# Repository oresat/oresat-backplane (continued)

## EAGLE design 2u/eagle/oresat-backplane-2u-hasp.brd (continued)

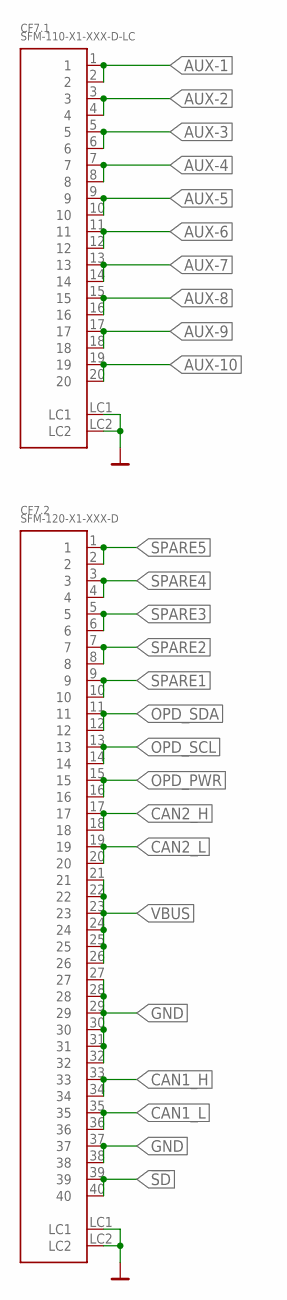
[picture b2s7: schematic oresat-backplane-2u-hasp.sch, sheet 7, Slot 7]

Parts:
CF7.1: SFM-110-X1-XXX-D-LC
CF7.2: SFM-120-X1-XXX-D

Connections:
!SD: CF7.2.39, CF7.2.40; also elsewhere on the board
AUX-1: CF7.1.1, CF7.1.2; also elsewhere on the board
AUX-2: CF7.1.3, CF7.1.4; also elsewhere on the board
AUX-3: CF7.1.5, CF7.1.6; also elsewhere on the board
AUX-4: CF7.1.7, CF7.1.8; also elsewhere on the board
AUX-5: CF7.1.9, CF7.1.10; also elsewhere on the board
AUX-6: CF7.1.11, CF7.1.12; also elsewhere on the board
AUX-7: CF7.1.13, CF7.1.14; also elsewhere on the board
AUX-8: CF7.1.15, CF7.1.16; also elsewhere on the board
AUX-9: CF7.1.17, CF7.1.18; also elsewhere on the board
AUX-10: CF7.1.19, CF7.1.20; also elsewhere on the board
CAN1_H: CF7.2.33, CF7.2.34; also elsewhere on the board
CAN1_L: CF7.2.35, CF7.2.36; also elsewhere on the board
CAN2_H: CF7.2.17, CF7.2.18; also elsewhere on the board
CAN2_L: CF7.2.19, CF7.2.20; also elsewhere on the board
GND: CF7.1.LC1, CF7.1.LC2, CF7.2.27, CF7.2.28, CF7.2.29, CF7.2.30, CF7.2.31, CF7.2.32, CF7.2.37, CF7.2.38, CF7.2.LC1, CF7.2.LC2; also elsewhere on the board
OPD_PWR: CF7.2.15, CF7.2.16; also elsewhere on the board
OPD_SCL: CF7.2.13, CF7.2.14; also elsewhere on the board
OPD_SDA: CF7.2.11, CF7.2.12; also elsewhere on the board
SPARE1: CF7.2.9, CF7.2.10; also elsewhere on the board
SPARE2: CF7.2.7, CF7.2.8; also elsewhere on the board
SPARE3: CF7.2.5, CF7.2.6; also elsewhere on the board
SPARE4: CF7.2.3, CF7.2.4; also elsewhere on the board
SPARE5: CF7.2.1, CF7.2.2; also elsewhere on the board
VBUS: CF7.2.21, CF7.2.22, CF7.2.23, CF7.2.24, CF7.2.25, CF7.2.26; also elsewhere on the board

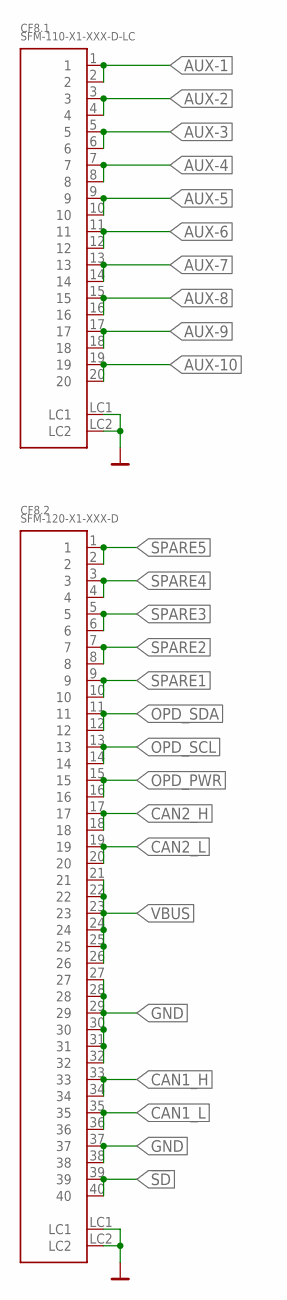
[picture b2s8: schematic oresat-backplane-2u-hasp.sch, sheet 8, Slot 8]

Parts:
CF8.1: SFM-110-X1-XXX-D-LC
CF8.2: SFM-120-X1-XXX-D

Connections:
!SD: CF8.2.39, CF8.2.40; also elsewhere on the board
AUX-1: CF8.1.1, CF8.1.2; also elsewhere on the board
AUX-2: CF8.1.3, CF8.1.4; also elsewhere on the board
AUX-3: CF8.1.5, CF8.1.6; also elsewhere on the board
AUX-4: CF8.1.7, CF8.1.8; also elsewhere on the board
AUX-5: CF8.1.9, CF8.1.10; also elsewhere on the board
AUX-6: CF8.1.11, CF8.1.12; also elsewhere on the board
AUX-7: CF8.1.13, CF8.1.14; also elsewhere on the board
AUX-8: CF8.1.15, CF8.1.16; also elsewhere on the board
AUX-9: CF8.1.17, CF8.1.18; also elsewhere on the board
AUX-10: CF8.1.19, CF8.1.20; also elsewhere on the board
CAN1_H: CF8.2.33, CF8.2.34; also elsewhere on the board
CAN1_L: CF8.2.35, CF8.2.36; also elsewhere on the board
CAN2_H: CF8.2.17, CF8.2.18; also elsewhere on the board
CAN2_L: CF8.2.19, CF8.2.20; also elsewhere on the board
GND: CF8.1.LC1, CF8.1.LC2, CF8.2.27, CF8.2.28, CF8.2.29, CF8.2.30, CF8.2.31, CF8.2.32, CF8.2.37, CF8.2.38, CF8.2.LC1, CF8.2.LC2; also elsewhere on the board
OPD_PWR: CF8.2.15, CF8.2.16; also elsewhere on the board
OPD_SCL: CF8.2.13, CF8.2.14; also elsewhere on the board
OPD_SDA: CF8.2.11, CF8.2.12; also elsewhere on the board
SPARE1: CF8.2.9, CF8.2.10; also elsewhere on the board
SPARE2: CF8.2.7, CF8.2.8; also elsewhere on the board
SPARE3: CF8.2.5, CF8.2.6; also elsewhere on the board
SPARE4: CF8.2.3, CF8.2.4; also elsewhere on the board
SPARE5: CF8.2.1, CF8.2.2; also elsewhere on the board
VBUS: CF8.2.21, CF8.2.22, CF8.2.23, CF8.2.24, CF8.2.25, CF8.2.26; also elsewhere on the board

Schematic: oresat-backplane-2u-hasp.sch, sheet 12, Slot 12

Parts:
CF12.1: SFM-110-X1-XXX-D-LC
CF12.2: SFM-120-X1-XXX-D

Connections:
!SD: CF12.2.39, CF12.2.40; also elsewhere on the board
AUX-1: CF12.1.1, CF12.1.2; also elsewhere on the board
AUX-2: CF12.1.3, CF12.1.4; also elsewhere on the board
AUX-3: CF12.1.5, CF12.1.6; also elsewhere on the board
AUX-4: CF12.1.7, CF12.1.8; also elsewhere on the board
AUX-5: CF12.1.9, CF12.1.10; also elsewhere on the board
AUX-6: CF12.1.11, CF12.1.12; also elsewhere on the board
AUX-7: CF12.1.13, CF12.1.14; also elsewhere on the board
AUX-8: CF12.1.15, CF12.1.16; also elsewhere on the board
AUX-9: CF12.1.17, CF12.1.18; also elsewhere on the board
AUX-10: CF12.1.19, CF12.1.20; also elsewhere on the board
CAN1_H: CF12.2.33, CF12.2.34; also elsewhere on the board
CAN1_L: CF12.2.35, CF12.2.36; also elsewhere on the board
CAN2_H: CF12.2.17, CF12.2.18; also elsewhere on the board
CAN2_L: CF12.2.19, CF12.2.20; also elsewhere on the board
GND: CF12.1.LC1, CF12.1.LC2, CF12.2.27, CF12.2.28, CF12.2.29, CF12.2.30, CF12.2.31, CF12.2.32, CF12.2.37, CF12.2.38, CF12.2.LC1, CF12.2.LC2; also elsewhere on the board
OPD_PWR: CF12.2.15, CF12.2.16; also elsewhere on the board
OPD_SCL: CF12.2.13, CF12.2.14; also elsewhere on the board
OPD_SDA: CF12.2.11, CF12.2.12; also elsewhere on the board
SPARE1: CF12.2.9, CF12.2.10; also elsewhere on the board
SPARE2: CF12.2.7, CF12.2.8; also elsewhere on the board
SPARE3: CF12.2.5, CF12.2.6; also elsewhere on the board
SPARE4: CF12.2.3, CF12.2.4; also elsewhere on the board
SPARE5: CF12.2.1, CF12.2.2; also elsewhere on the board
VBUS: CF12.2.21, CF12.2.22, CF12.2.23, CF12.2.24, CF12.2.25, CF12.2.26; also elsewhere on the board

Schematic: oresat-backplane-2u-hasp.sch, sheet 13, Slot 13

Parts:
CF13.1: SFM-110-X1-XXX-D-LC
CF13.2: SFM-120-X1-XXX-D

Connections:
!SD: CF13.2.39, CF13.2.40; also elsewhere on the board
AUX-1: CF13.1.1, CF13.1.2; also elsewhere on the board
AUX-2: CF13.1.3, CF13.1.4; also elsewhere on the board
AUX-3: CF13.1.5, CF13.1.6; also elsewhere on the board
AUX-4: CF13.1.7, CF13.1.8; also elsewhere on the board
AUX-5: CF13.1.9, CF13.1.10; also elsewhere on the board
AUX-6: CF13.1.11, CF13.1.12; also elsewhere on the board
AUX-7: CF13.1.13, CF13.1.14; also elsewhere on the board
AUX-8: CF13.1.15, CF13.1.16; also elsewhere on the board
AUX-9: CF13.1.17, CF13.1.18; also elsewhere on the board
AUX-10: CF13.1.19, CF13.1.20; also elsewhere on the board
CAN1_H: CF13.2.33, CF13.2.34; also elsewhere on the board
CAN1_L: CF13.2.35, CF13.2.36; also elsewhere on the board
CAN2_H: CF13.2.17, CF13.2.18; also elsewhere on the board
CAN2_L: CF13.2.19, CF13.2.20; also elsewhere on the board
GND: CF13.1.LC1, CF13.1.LC2, CF13.2.27, CF13.2.28, CF13.2.29, CF13.2.30, CF13.2.31, CF13.2.32, CF13.2.37, CF13.2.38, CF13.2.LC1, CF13.2.LC2; also elsewhere on the board
OPD_PWR: CF13.2.15, CF13.2.16; also elsewhere on the board
OPD_SCL: CF13.2.13, CF13.2.14; also elsewhere on the board
OPD_SDA: CF13.2.11, CF13.2.12; also elsewhere on the board
SPARE1: CF13.2.9, CF13.2.10; also elsewhere on the board
SPARE2: CF13.2.7, CF13.2.8; also elsewhere on the board
SPARE3: CF13.2.5, CF13.2.6; also elsewhere on the board
SPARE4: CF13.2.3, CF13.2.4; also elsewhere on the board
SPARE5: CF13.2.1, CF13.2.2; also elsewhere on the board
VBUS: CF13.2.21, CF13.2.22, CF13.2.23, CF13.2.24, CF13.2.25, CF13.2.26; also elsewhere on the board

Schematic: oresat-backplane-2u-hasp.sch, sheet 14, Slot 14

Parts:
CF14.1: SFM-110-X1-XXX-D-LC
CF14.2: SFM-120-X1-XXX-D

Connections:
!SD: CF14.2.39, CF14.2.40; also elsewhere on the board
AUX-1: CF14.1.1, CF14.1.2; also elsewhere on the board
AUX-2: CF14.1.3, CF14.1.4; also elsewhere on the board
AUX-3: CF14.1.5, CF14.1.6; also elsewhere on the board
AUX-4: CF14.1.7, CF14.1.8; also elsewhere on the board
AUX-5: CF14.1.9, CF14.1.10; also elsewhere on the board
AUX-6: CF14.1.11, CF14.1.12; also elsewhere on the board
AUX-7: CF14.1.13, CF14.1.14; also elsewhere on the board
AUX-8: CF14.1.15, CF14.1.16; also elsewhere on the board
AUX-9: CF14.1.17, CF14.1.18; also elsewhere on the board
AUX-10: CF14.1.19, CF14.1.20; also elsewhere on the board
CAN1_H: CF14.2.33, CF14.2.34; also elsewhere on the board
CAN1_L: CF14.2.35, CF14.2.36; also elsewhere on the board
CAN2_H: CF14.2.17, CF14.2.18; also elsewhere on the board
CAN2_L: CF14.2.19, CF14.2.20; also elsewhere on the board
GND: CF14.1.LC1, CF14.1.LC2, CF14.2.27, CF14.2.28, CF14.2.29, CF14.2.30, CF14.2.31, CF14.2.32, CF14.2.37, CF14.2.38, CF14.2.LC1, CF14.2.LC2; also elsewhere on the board
OPD_PWR: CF14.2.15, CF14.2.16; also elsewhere on the board
OPD_SCL: CF14.2.13, CF14.2.14; also elsewhere on the board
OPD_SDA: CF14.2.11, CF14.2.12; also elsewhere on the board
SPARE1: CF14.2.9, CF14.2.10; also elsewhere on the board
SPARE2: CF14.2.7, CF14.2.8; also elsewhere on the board
SPARE3: CF14.2.5, CF14.2.6; also elsewhere on the board
SPARE4: CF14.2.3, CF14.2.4; also elsewhere on the board
SPARE5: CF14.2.1, CF14.2.2; also elsewhere on the board
VBUS: CF14.2.21, CF14.2.22, CF14.2.23, CF14.2.24, CF14.2.25, CF14.2.26; also elsewhere on the board

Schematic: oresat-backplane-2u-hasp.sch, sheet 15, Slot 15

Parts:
CF15.1: SFM-110-X1-XXX-D-LC
CF15.2: SFM-120-X1-XXX-D

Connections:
!SD: CF15.2.39, CF15.2.40; also elsewhere on the board
AUX-1: CF15.1.1, CF15.1.2; also elsewhere on the board
AUX-2: CF15.1.3, CF15.1.4; also elsewhere on the board
AUX-3: CF15.1.5, CF15.1.6; also elsewhere on the board
AUX-4: CF15.1.7, CF15.1.8; also elsewhere on the board
AUX-5: CF15.1.9, CF15.1.10; also elsewhere on the board
AUX-6: CF15.1.11, CF15.1.12; also elsewhere on the board
AUX-7: CF15.1.13, CF15.1.14; also elsewhere on the board
AUX-8: CF15.1.15, CF15.1.16; also elsewhere on the board
AUX-9: CF15.1.17, CF15.1.18; also elsewhere on the board
AUX-10: CF15.1.19, CF15.1.20; also elsewhere on the board
CAN1_H: CF15.2.33, CF15.2.34; also elsewhere on the board
CAN1_L: CF15.2.35, CF15.2.36; also elsewhere on the board
CAN2_H: CF15.2.17, CF15.2.18; also elsewhere on the board
CAN2_L: CF15.2.19, CF15.2.20; also elsewhere on the board
GND: CF15.1.LC1, CF15.1.LC2, CF15.2.27, CF15.2.28, CF15.2.29, CF15.2.30, CF15.2.31, CF15.2.32, CF15.2.37, CF15.2.38, CF15.2.LC1, CF15.2.LC2; also elsewhere on the board
OPD_PWR: CF15.2.15, CF15.2.16; also elsewhere on the board
OPD_SCL: CF15.2.13, CF15.2.14; also elsewhere on the board
OPD_SDA: CF15.2.11, CF15.2.12; also elsewhere on the board
SPARE1: CF15.2.9, CF15.2.10; also elsewhere on the board
SPARE2: CF15.2.7, CF15.2.8; also elsewhere on the board
SPARE3: CF15.2.5, CF15.2.6; also elsewhere on the board
SPARE4: CF15.2.3, CF15.2.4; also elsewhere on the board
SPARE5: CF15.2.1, CF15.2.2; also elsewhere on the board
VBUS: CF15.2.21, CF15.2.22, CF15.2.23, CF15.2.24, CF15.2.25, CF15.2.26; also elsewhere on the board

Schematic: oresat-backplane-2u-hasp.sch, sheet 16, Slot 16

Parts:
CF16.1: SFM-110-X1-XXX-D-LC
CF16.2: SFM-120-X1-XXX-D

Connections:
!SD: CF16.2.39, CF16.2.40; also elsewhere on the board
AUX-1: CF16.1.1, CF16.1.2; also elsewhere on the board
AUX-2: CF16.1.3, CF16.1.4; also elsewhere on the board
AUX-3: CF16.1.5, CF16.1.6; also elsewhere on the board
AUX-4: CF16.1.7, CF16.1.8; also elsewhere on the board
AUX-5: CF16.1.9, CF16.1.10; also elsewhere on the board
AUX-6: CF16.1.11, CF16.1.12; also elsewhere on the board
AUX-7: CF16.1.13, CF16.1.14; also elsewhere on the board
AUX-8: CF16.1.15, CF16.1.16; also elsewhere on the board
AUX-9: CF16.1.17, CF16.1.18; also elsewhere on the board
AUX-10: CF16.1.19, CF16.1.20; also elsewhere on the board
CAN1_H: CF16.2.33, CF16.2.34; also elsewhere on the board
CAN1_L: CF16.2.35, CF16.2.36; also elsewhere on the board
CAN2_H: CF16.2.17, CF16.2.18; also elsewhere on the board
CAN2_L: CF16.2.19, CF16.2.20; also elsewhere on the board
GND: CF16.1.LC1, CF16.1.LC2, CF16.2.27, CF16.2.28, CF16.2.29, CF16.2.30, CF16.2.31, CF16.2.32, CF16.2.37, CF16.2.38, CF16.2.LC1, CF16.2.LC2; also elsewhere on the board
OPD_PWR: CF16.2.15, CF16.2.16; also elsewhere on the board
OPD_SCL: CF16.2.13, CF16.2.14; also elsewhere on the board
OPD_SDA: CF16.2.11, CF16.2.12; also elsewhere on the board
SPARE1: CF16.2.9, CF16.2.10; also elsewhere on the board
SPARE2: CF16.2.7, CF16.2.8; also elsewhere on the board
SPARE3: CF16.2.5, CF16.2.6; also elsewhere on the board
SPARE4: CF16.2.3, CF16.2.4; also elsewhere on the board
SPARE5: CF16.2.1, CF16.2.2; also elsewhere on the board
VBUS: CF16.2.21, CF16.2.22, CF16.2.23, CF16.2.24, CF16.2.25, CF16.2.26; also elsewhere on the board

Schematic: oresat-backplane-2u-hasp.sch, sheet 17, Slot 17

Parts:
CF17.1: SFM-110-X1-XXX-D-LC
CF17.2: SFM-120-X1-XXX-D

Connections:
!SD: CF17.2.39, CF17.2.40; also elsewhere on the board
AUX-1: CF17.1.1, CF17.1.2; also elsewhere on the board
AUX-2: CF17.1.3, CF17.1.4; also elsewhere on the board
AUX-3: CF17.1.5, CF17.1.6; also elsewhere on the board
AUX-4: CF17.1.7, CF17.1.8; also elsewhere on the board
AUX-5: CF17.1.9, CF17.1.10; also elsewhere on the board
AUX-6: CF17.1.11, CF17.1.12; also elsewhere on the board
AUX-7: CF17.1.13, CF17.1.14; also elsewhere on the board
AUX-8: CF17.1.15, CF17.1.16; also elsewhere on the board
AUX-9: CF17.1.17, CF17.1.18; also elsewhere on the board
AUX-10: CF17.1.19, CF17.1.20; also elsewhere on the board
CAN1_H: CF17.2.33, CF17.2.34; also elsewhere on the board
CAN1_L: CF17.2.35, CF17.2.36; also elsewhere on the board
CAN2_H: CF17.2.17, CF17.2.18; also elsewhere on the board
CAN2_L: CF17.2.19, CF17.2.20; also elsewhere on the board
GND: CF17.1.LC1, CF17.1.LC2, CF17.2.27, CF17.2.28, CF17.2.29, CF17.2.30, CF17.2.31, CF17.2.32, CF17.2.37, CF17.2.38, CF17.2.LC1, CF17.2.LC2; also elsewhere on the board
OPD_PWR: CF17.2.15, CF17.2.16; also elsewhere on the board
OPD_SCL: CF17.2.13, CF17.2.14; also elsewhere on the board
OPD_SDA: CF17.2.11, CF17.2.12; also elsewhere on the board
SPARE1: CF17.2.9, CF17.2.10; also elsewhere on the board
SPARE2: CF17.2.7, CF17.2.8; also elsewhere on the board
SPARE3: CF17.2.5, CF17.2.6; also elsewhere on the board
SPARE4: CF17.2.3, CF17.2.4; also elsewhere on the board
SPARE5: CF17.2.1, CF17.2.2; also elsewhere on the board
VBUS: CF17.2.21, CF17.2.22, CF17.2.23, CF17.2.24, CF17.2.25, CF17.2.26; also elsewhere on the board

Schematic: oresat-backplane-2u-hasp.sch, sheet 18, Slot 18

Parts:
CF18.1: SFM-110-X1-XXX-D-LC
CF18.2: SFM-120-X1-XXX-D

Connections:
!SD: CF18.2.39, CF18.2.40; also elsewhere on the board
AUX-1: CF18.1.1, CF18.1.2; also elsewhere on the board
AUX-2: CF18.1.3, CF18.1.4; also elsewhere on the board
AUX-3: CF18.1.5, CF18.1.6; also elsewhere on the board
AUX-4: CF18.1.7, CF18.1.8; also elsewhere on the board
AUX-5: CF18.1.9, CF18.1.10; also elsewhere on the board
AUX-6: CF18.1.11, CF18.1.12; also elsewhere on the board
AUX-7: CF18.1.13, CF18.1.14; also elsewhere on the board
AUX-8: CF18.1.15, CF18.1.16; also elsewhere on the board
AUX-9: CF18.1.17, CF18.1.18; also elsewhere on the board
AUX-10: CF18.1.19, CF18.1.20; also elsewhere on the board
CAN1_H: CF18.2.33, CF18.2.34; also elsewhere on the board
CAN1_L: CF18.2.35, CF18.2.36; also elsewhere on the board
CAN2_H: CF18.2.17, CF18.2.18; also elsewhere on the board
CAN2_L: CF18.2.19, CF18.2.20; also elsewhere on the board
GND: CF18.1.LC1, CF18.1.LC2, CF18.2.27, CF18.2.28, CF18.2.29, CF18.2.30, CF18.2.31, CF18.2.32, CF18.2.37, CF18.2.38, CF18.2.LC1, CF18.2.LC2; also elsewhere on the board
OPD_PWR: CF18.2.15, CF18.2.16; also elsewhere on the board
OPD_SCL: CF18.2.13, CF18.2.14; also elsewhere on the board
OPD_SDA: CF18.2.11, CF18.2.12; also elsewhere on the board
SPARE1: CF18.2.9, CF18.2.10; also elsewhere on the board
SPARE2: CF18.2.7, CF18.2.8; also elsewhere on the board
SPARE3: CF18.2.5, CF18.2.6; also elsewhere on the board
SPARE4: CF18.2.3, CF18.2.4; also elsewhere on the board
SPARE5: CF18.2.1, CF18.2.2; also elsewhere on the board
VBUS: CF18.2.21, CF18.2.22, CF18.2.23, CF18.2.24, CF18.2.25, CF18.2.26; also elsewhere on the board

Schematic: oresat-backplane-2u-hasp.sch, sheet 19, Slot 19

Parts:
CF19.1: SFM-110-X1-XXX-D-LC
CF19.2: SFM-120-X1-XXX-D

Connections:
!SD: CF19.2.39, CF19.2.40; also elsewhere on the board
AUX-1: CF19.1.1, CF19.1.2; also elsewhere on the board
AUX-2: CF19.1.3, CF19.1.4; also elsewhere on the board
AUX-3: CF19.1.5, CF19.1.6; also elsewhere on the board
AUX-4: CF19.1.7, CF19.1.8; also elsewhere on the board
AUX-5: CF19.1.9, CF19.1.10; also elsewhere on the board
AUX-6: CF19.1.11, CF19.1.12; also elsewhere on the board
AUX-7: CF19.1.13, CF19.1.14; also elsewhere on the board
AUX-8: CF19.1.15, CF19.1.16; also elsewhere on the board
AUX-9: CF19.1.17, CF19.1.18; also elsewhere on the board
AUX-10: CF19.1.19, CF19.1.20; also elsewhere on the board
CAN1_H: CF19.2.33, CF19.2.34; also elsewhere on the board
CAN1_L: CF19.2.35, CF19.2.36; also elsewhere on the board
CAN2_H: CF19.2.17, CF19.2.18; also elsewhere on the board
CAN2_L: CF19.2.19, CF19.2.20; also elsewhere on the board
GND: CF19.1.LC1, CF19.1.LC2, CF19.2.27, CF19.2.28, CF19.2.29, CF19.2.30, CF19.2.31, CF19.2.32, CF19.2.37, CF19.2.38, CF19.2.LC1, CF19.2.LC2; also elsewhere on the board
OPD_PWR: CF19.2.15, CF19.2.16; also elsewhere on the board
OPD_SCL: CF19.2.13, CF19.2.14; also elsewhere on the board
OPD_SDA: CF19.2.11, CF19.2.12; also elsewhere on the board
SPARE1: CF19.2.9, CF19.2.10; also elsewhere on the board
SPARE2: CF19.2.7, CF19.2.8; also elsewhere on the board
SPARE3: CF19.2.5, CF19.2.6; also elsewhere on the board
SPARE4: CF19.2.3, CF19.2.4; also elsewhere on the board
SPARE5: CF19.2.1, CF19.2.2; also elsewhere on the board
VBUS: CF19.2.21, CF19.2.22, CF19.2.23, CF19.2.24, CF19.2.25, CF19.2.26; also elsewhere on the board

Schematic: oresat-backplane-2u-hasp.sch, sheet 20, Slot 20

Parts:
C3, C4: 1n; .0603-C-NOSILK
CF2.4: SFM-120-X1-XXX-D
CM20.1, CM20.2, CM20.3: J-MOLEX-SMPM-73300-0111X
R5, R6, R7, R8: 60.4; 1206-C

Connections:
!SD: CF2.4.39, CF2.4.40; also elsewhere on the board
CAN1_H: CF2.4.33, CF2.4.34, R5.1; also elsewhere on the board
CAN1_L: CF2.4.35, CF2.4.36, R6.1; also elsewhere on the board
CAN2_H: CF2.4.17, CF2.4.18, R7.1; also elsewhere on the board
CAN2_L: CF2.4.19, CF2.4.20, R8.1; also elsewhere on the board
GND: C3.2, C4.2, CF2.4.27, CF2.4.28, CF2.4.29, CF2.4.30, CF2.4.31, CF2.4.32, CF2.4.37, CF2.4.38, CF2.4.LC1, CF2.4.LC2, CM20.1.P$1 (SHIELD1), CM20.1.P$2 (SHIELD1), CM20.1.P$3 (SHIELD1), CM20.1.P$4 (SHIELD1), CM20.2.P$1 (SHIELD1), CM20.2.P$2 (SHIELD1), CM20.2.P$3 (SHIELD1), CM20.2.P$4 (SHIELD1), CM20.3.P$1 (SHIELD1), CM20.3.P$2 (SHIELD1), CM20.3.P$3 (SHIELD1), CM20.3.P$4 (SHIELD1); also elsewhere on the board
L-TURNSTILE: CM20.1.RF-DOWN (RF); also elsewhere on the board
unnamed: C4.1, R7.2, R8.2
unnamed: C3.1, R5.2, R6.2
OPD_PWR: CF2.4.15, CF2.4.16; also elsewhere on the board
OPD_SCL: CF2.4.13, CF2.4.14; also elsewhere on the board
OPD_SDA: CF2.4.11, CF2.4.12; also elsewhere on the board
S-TURNSTILE: CM20.3.RF-DOWN (RF); also elsewhere on the board
SPARE1: CF2.4.9, CF2.4.10; also elsewhere on the board
SPARE2: CF2.4.7, CF2.4.8; also elsewhere on the board
SPARE3: CF2.4.5, CF2.4.6; also elsewhere on the board
SPARE4: CF2.4.3, CF2.4.4; also elsewhere on the board
SPARE5: CF2.4.1, CF2.4.2; also elsewhere on the board
U-TURNSTILE: CM20.2.RF-DOWN (RF); also elsewhere on the board
VBUS: CF2.4.21, CF2.4.22, CF2.4.23, CF2.4.24, CF2.4.25, CF2.4.26; also elsewhere on the board

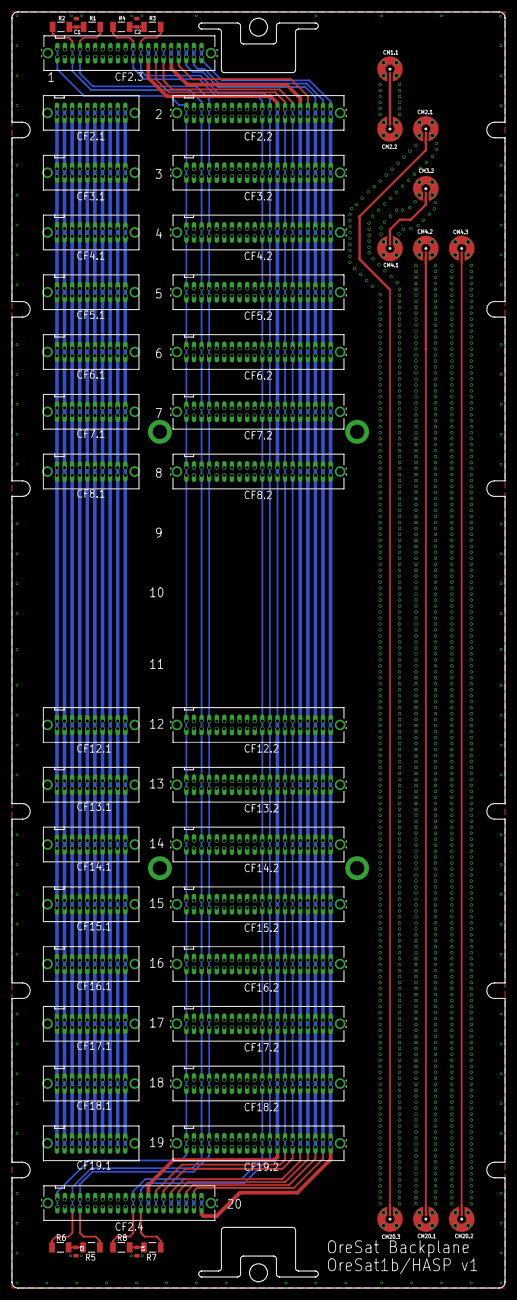
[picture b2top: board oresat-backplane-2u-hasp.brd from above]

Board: 4 copper layers, 82.5 x 213.5 mm, 54 parts (0 on the bottom side), 34 nets.

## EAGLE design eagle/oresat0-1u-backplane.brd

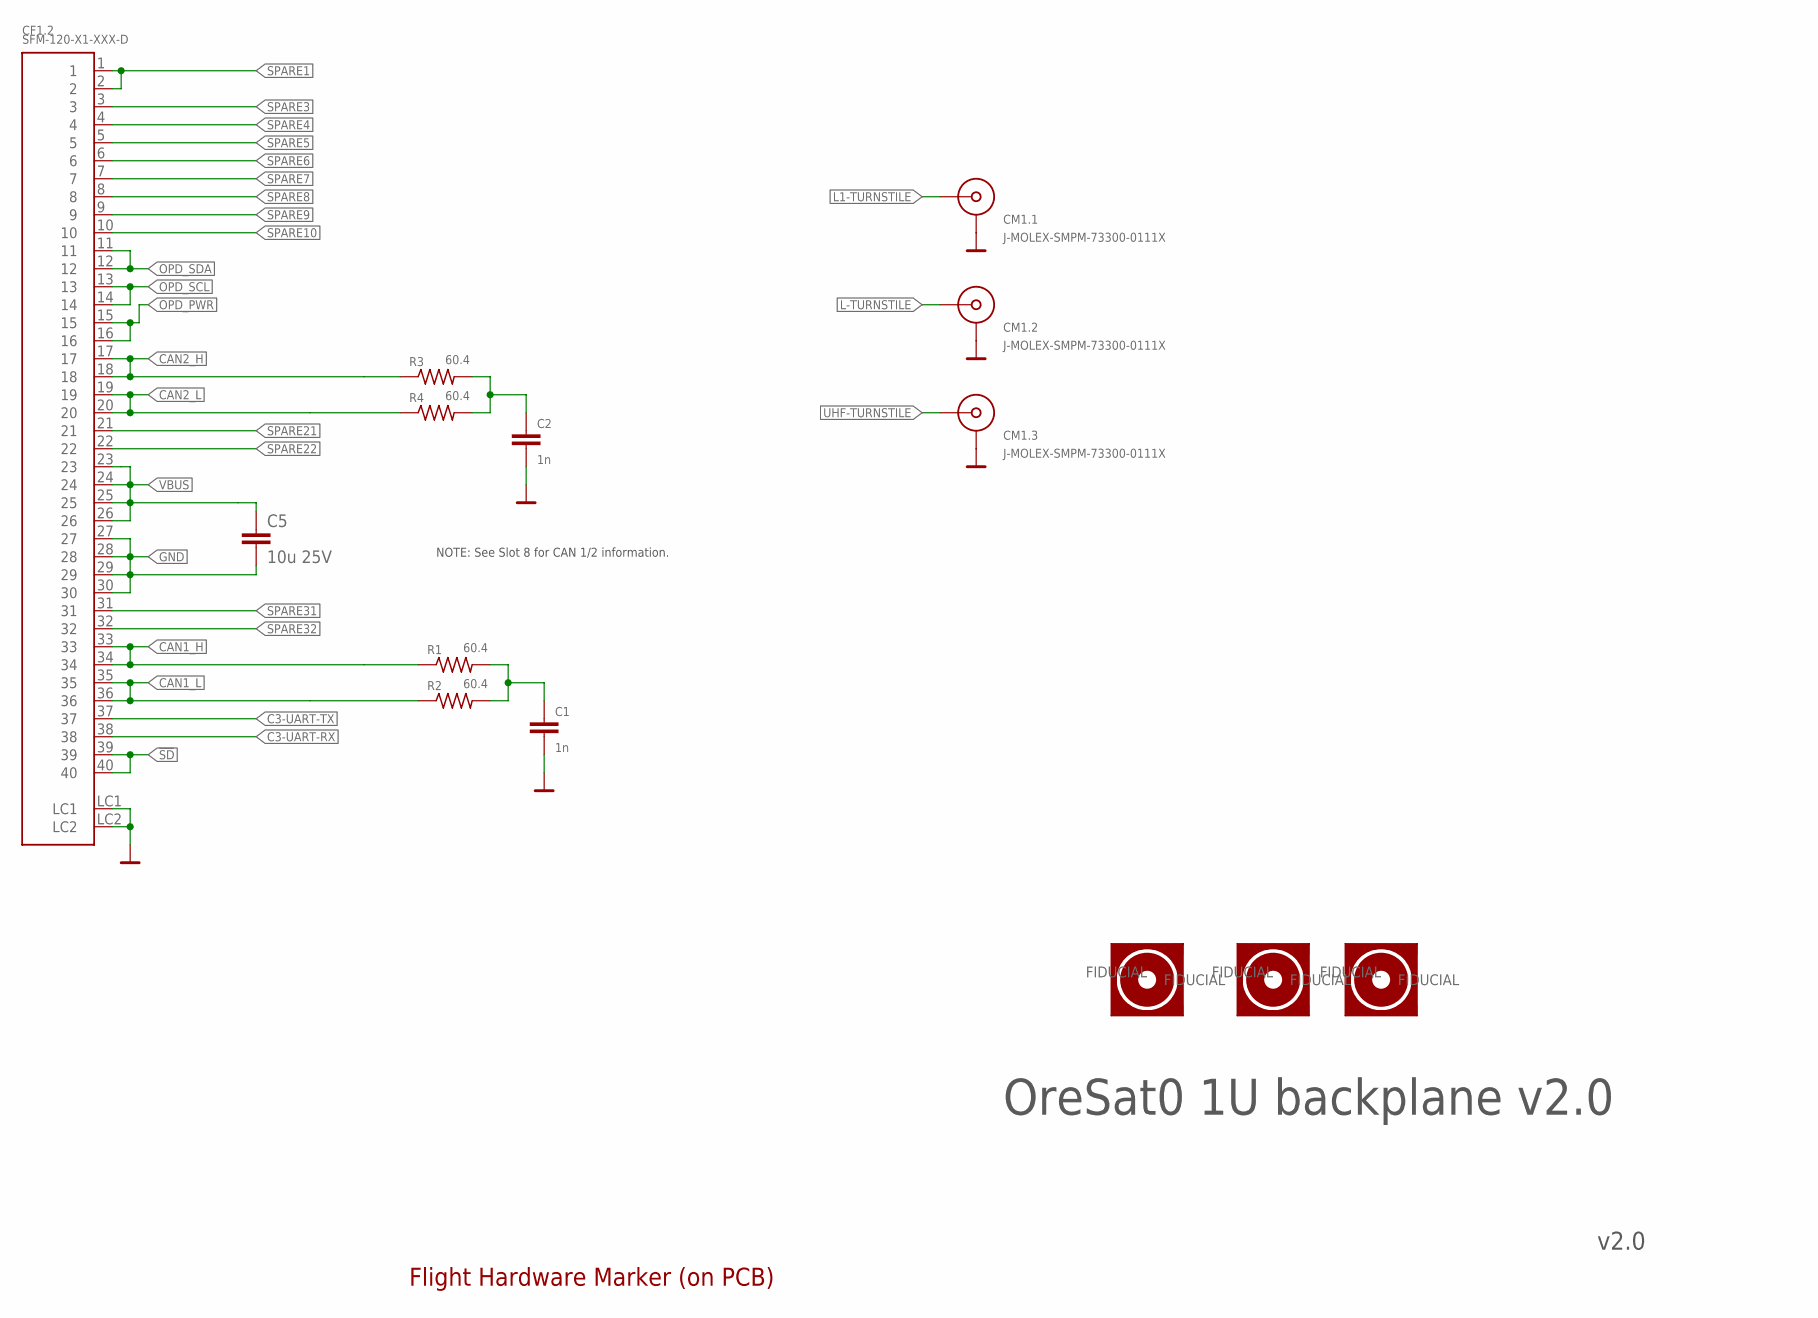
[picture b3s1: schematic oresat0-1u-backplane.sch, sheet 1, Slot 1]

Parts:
C1, C2: 1n; .0603-C-NOSILK
C5: 10u 25V; 1206-B
CF1.2: SFM-120-X1-XXX-D
CM1.1, CM1.2, CM1.3: J-MOLEX-SMPM-73300-0111X
FIDUCIAL1, FIDUCIAL2, FIDUCIAL3: FIDUCIAL-1.0X2.0
R1, R2, R3, R4: 60.4; 1206-C
U$1: FLIGHMARKERNEW; FLIGHTMARKER_NEW_BOARDS

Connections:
!SD: CF1.2.39, CF1.2.40; also elsewhere on the board
C3-UART-RX: CF1.2.38; also elsewhere on the board
C3-UART-TX: CF1.2.37; also elsewhere on the board
CAN1_H: CF1.2.33, CF1.2.34, R1.1; also elsewhere on the board
CAN1_L: CF1.2.35, CF1.2.36, R2.1; also elsewhere on the board
CAN2_H: CF1.2.17, CF1.2.18, R3.1; also elsewhere on the board
CAN2_L: CF1.2.19, CF1.2.20, R4.1; also elsewhere on the board
GND: C1.2, C2.2, C5.2, CF1.2.27, CF1.2.28, CF1.2.29, CF1.2.30, CF1.2.LC1, CF1.2.LC2, CM1.1.P$1 (SHIELD1), CM1.1.P$2 (SHIELD1), CM1.1.P$3 (SHIELD1), CM1.1.P$4 (SHIELD1), CM1.2.P$1 (SHIELD1), CM1.2.P$2 (SHIELD1), CM1.2.P$3 (SHIELD1), CM1.2.P$4 (SHIELD1), CM1.3.P$1 (SHIELD1), CM1.3.P$2 (SHIELD1), CM1.3.P$3 (SHIELD1), CM1.3.P$4 (SHIELD1); also elsewhere on the board
L1-TURNSTILE: CM1.1.RF-DOWN (RF); also elsewhere on the board
L-TURNSTILE: CM1.2.RF-DOWN (RF); also elsewhere on the board
unnamed: C2.1, R3.2, R4.2
unnamed: C1.1, R1.2, R2.2
OPD_PWR: CF1.2.15, CF1.2.16; also elsewhere on the board
OPD_SCL: CF1.2.13, CF1.2.14; also elsewhere on the board
OPD_SDA: CF1.2.11, CF1.2.12; also elsewhere on the board
SPARE1: CF1.2.1, CF1.2.2; also elsewhere on the board
SPARE3: CF1.2.3; also elsewhere on the board
SPARE4: CF1.2.4; also elsewhere on the board
SPARE5: CF1.2.5; also elsewhere on the board
SPARE6: CF1.2.6; also elsewhere on the board
SPARE7: CF1.2.7; also elsewhere on the board
SPARE8: CF1.2.8; also elsewhere on the board
SPARE9: CF1.2.9; also elsewhere on the board
SPARE10: CF1.2.10; also elsewhere on the board
SPARE21: CF1.2.21; also elsewhere on the board
SPARE22: CF1.2.22; also elsewhere on the board
SPARE31: CF1.2.31; also elsewhere on the board
SPARE32: CF1.2.32; also elsewhere on the board
UHF-TURNSTILE: CM1.3.RF-DOWN (RF); also elsewhere on the board
VBUS: C5.1, CF1.2.23, CF1.2.24, CF1.2.25, CF1.2.26; also elsewhere on the board

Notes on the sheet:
v2.0
NOTE: See Slot 8 for CAN 1/2 information.
OreSat0 1U backplane v2.0

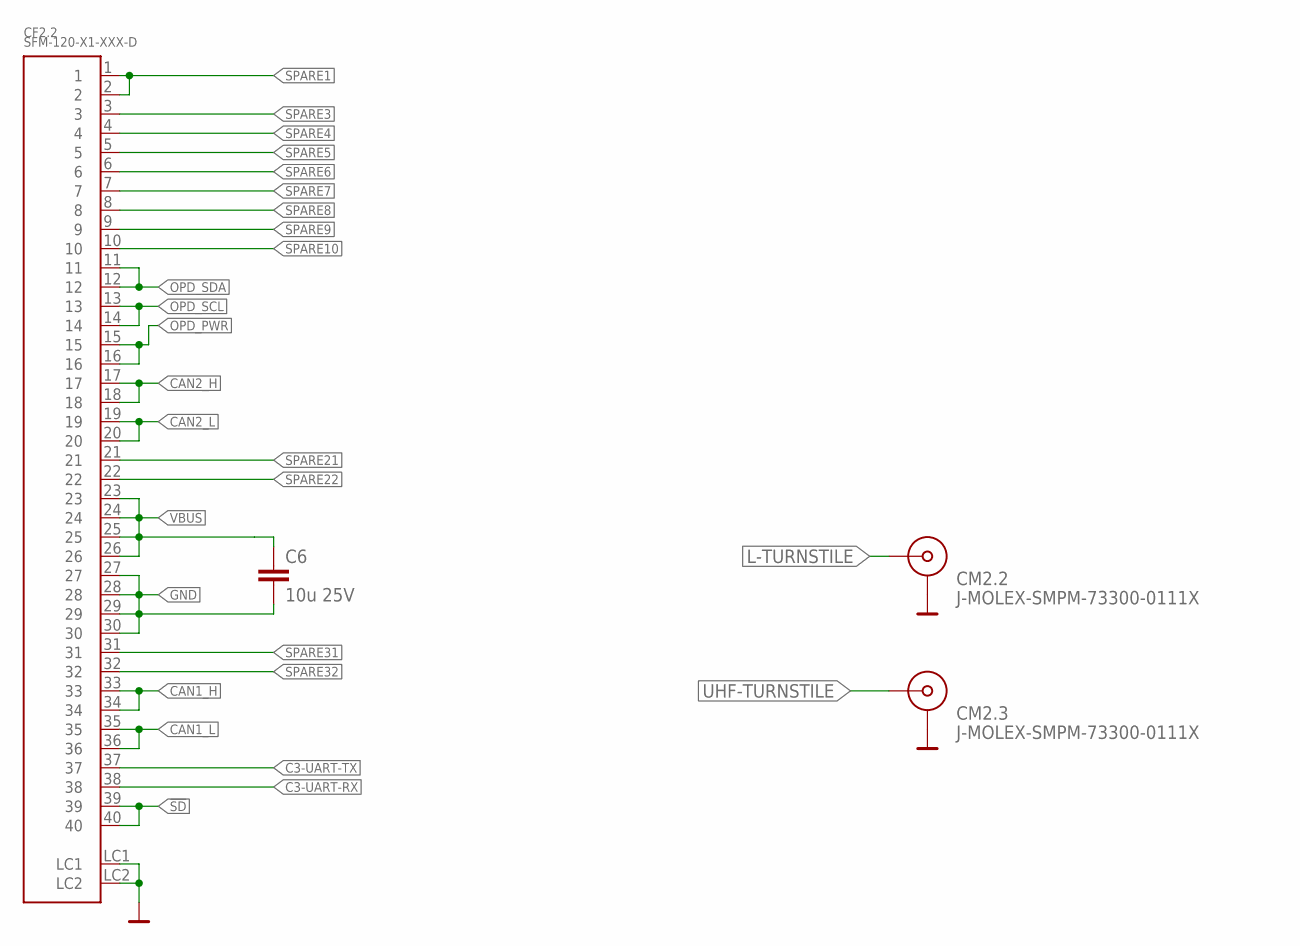
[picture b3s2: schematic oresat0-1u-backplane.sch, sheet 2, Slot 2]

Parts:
C6: 10u 25V; 1206-B
CF2.2: SFM-120-X1-XXX-D
CM2.2, CM2.3: J-MOLEX-SMPM-73300-0111X

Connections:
!SD: CF2.2.39, CF2.2.40; also elsewhere on the board
C3-UART-RX: CF2.2.38; also elsewhere on the board
C3-UART-TX: CF2.2.37; also elsewhere on the board
CAN1_H: CF2.2.33, CF2.2.34; also elsewhere on the board
CAN1_L: CF2.2.35, CF2.2.36; also elsewhere on the board
CAN2_H: CF2.2.17, CF2.2.18; also elsewhere on the board
CAN2_L: CF2.2.19, CF2.2.20; also elsewhere on the board
GND: C6.2, CF2.2.27, CF2.2.28, CF2.2.29, CF2.2.30, CF2.2.LC1, CF2.2.LC2, CM2.2.P$1 (SHIELD1), CM2.2.P$2 (SHIELD1), CM2.2.P$3 (SHIELD1), CM2.2.P$4 (SHIELD1), CM2.3.P$1 (SHIELD1), CM2.3.P$2 (SHIELD1), CM2.3.P$3 (SHIELD1), CM2.3.P$4 (SHIELD1); also elsewhere on the board
L-TURNSTILE: CM2.2.RF-DOWN (RF); also elsewhere on the board
OPD_PWR: CF2.2.15, CF2.2.16; also elsewhere on the board
OPD_SCL: CF2.2.13, CF2.2.14; also elsewhere on the board
OPD_SDA: CF2.2.11, CF2.2.12; also elsewhere on the board
SPARE1: CF2.2.1, CF2.2.2; also elsewhere on the board
SPARE3: CF2.2.3; also elsewhere on the board
SPARE4: CF2.2.4; also elsewhere on the board
SPARE5: CF2.2.5; also elsewhere on the board
SPARE6: CF2.2.6; also elsewhere on the board
SPARE7: CF2.2.7; also elsewhere on the board
SPARE8: CF2.2.8; also elsewhere on the board
SPARE9: CF2.2.9; also elsewhere on the board
SPARE10: CF2.2.10; also elsewhere on the board
SPARE21: CF2.2.21; also elsewhere on the board
SPARE22: CF2.2.22; also elsewhere on the board
SPARE31: CF2.2.31; also elsewhere on the board
SPARE32: CF2.2.32; also elsewhere on the board
UHF-TURNSTILE: CM2.3.RF-DOWN (RF); also elsewhere on the board
VBUS: C6.1, CF2.2.23, CF2.2.24, CF2.2.25, CF2.2.26; also elsewhere on the board

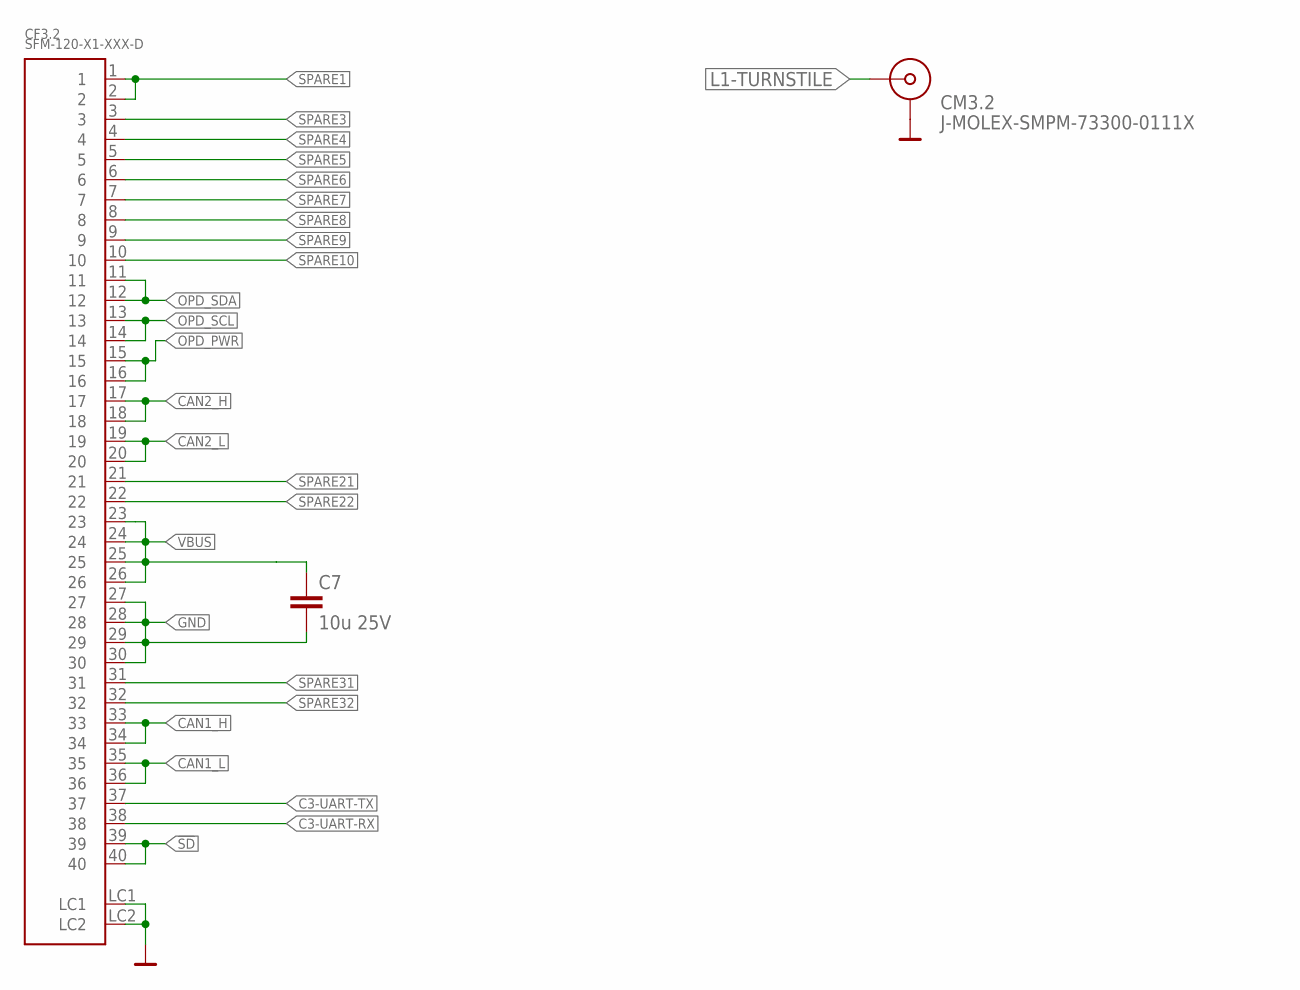
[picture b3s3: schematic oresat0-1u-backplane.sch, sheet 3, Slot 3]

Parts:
C7: 10u 25V; 1206-B
CF3.2: SFM-120-X1-XXX-D
CM3.2: J-MOLEX-SMPM-73300-0111X

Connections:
!SD: CF3.2.39, CF3.2.40; also elsewhere on the board
C3-UART-RX: CF3.2.38; also elsewhere on the board
C3-UART-TX: CF3.2.37; also elsewhere on the board
CAN1_H: CF3.2.33, CF3.2.34; also elsewhere on the board
CAN1_L: CF3.2.35, CF3.2.36; also elsewhere on the board
CAN2_H: CF3.2.17, CF3.2.18; also elsewhere on the board
CAN2_L: CF3.2.19, CF3.2.20; also elsewhere on the board
GND: C7.2, CF3.2.27, CF3.2.28, CF3.2.29, CF3.2.30, CF3.2.LC1, CF3.2.LC2, CM3.2.P$1 (SHIELD1), CM3.2.P$2 (SHIELD1), CM3.2.P$3 (SHIELD1), CM3.2.P$4 (SHIELD1); also elsewhere on the board
L1-TURNSTILE: CM3.2.RF-DOWN (RF); also elsewhere on the board
OPD_PWR: CF3.2.15, CF3.2.16; also elsewhere on the board
OPD_SCL: CF3.2.13, CF3.2.14; also elsewhere on the board
OPD_SDA: CF3.2.11, CF3.2.12; also elsewhere on the board
SPARE1: CF3.2.1, CF3.2.2; also elsewhere on the board
SPARE3: CF3.2.3; also elsewhere on the board
SPARE4: CF3.2.4; also elsewhere on the board
SPARE5: CF3.2.5; also elsewhere on the board
SPARE6: CF3.2.6; also elsewhere on the board
SPARE7: CF3.2.7; also elsewhere on the board
SPARE8: CF3.2.8; also elsewhere on the board
SPARE9: CF3.2.9; also elsewhere on the board
SPARE10: CF3.2.10; also elsewhere on the board
SPARE21: CF3.2.21; also elsewhere on the board
SPARE22: CF3.2.22; also elsewhere on the board
SPARE31: CF3.2.31; also elsewhere on the board
SPARE32: CF3.2.32; also elsewhere on the board
VBUS: C7.1, CF3.2.23, CF3.2.24, CF3.2.25, CF3.2.26; also elsewhere on the board
